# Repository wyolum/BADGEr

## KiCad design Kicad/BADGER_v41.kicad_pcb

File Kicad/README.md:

BADGEr
======

EReader badge and shield
new version (v4.1) with minor mods to the front silk legend. No hardware changes from v4

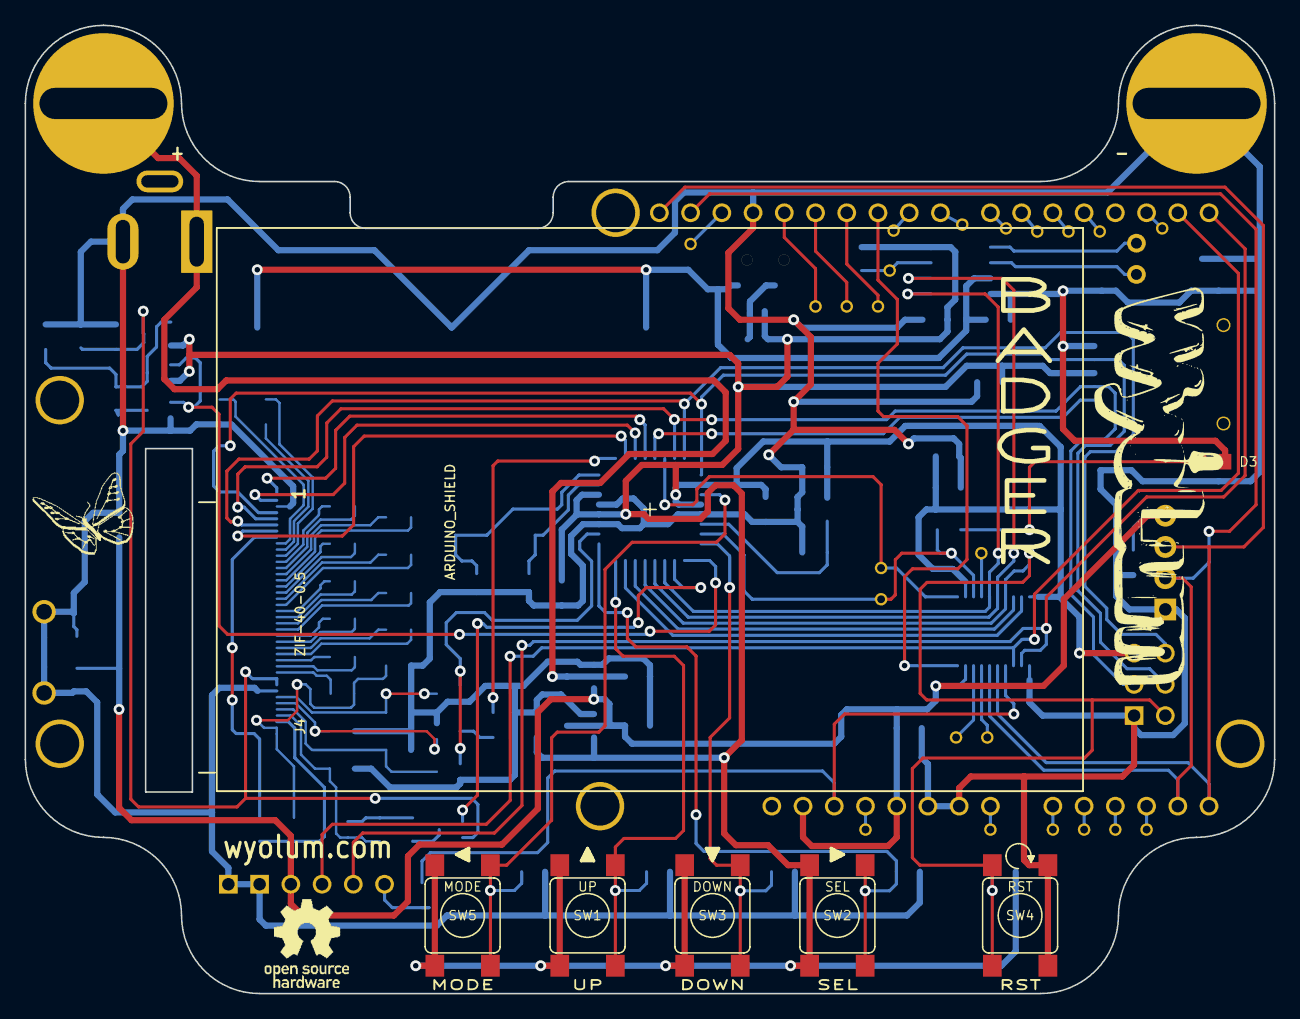
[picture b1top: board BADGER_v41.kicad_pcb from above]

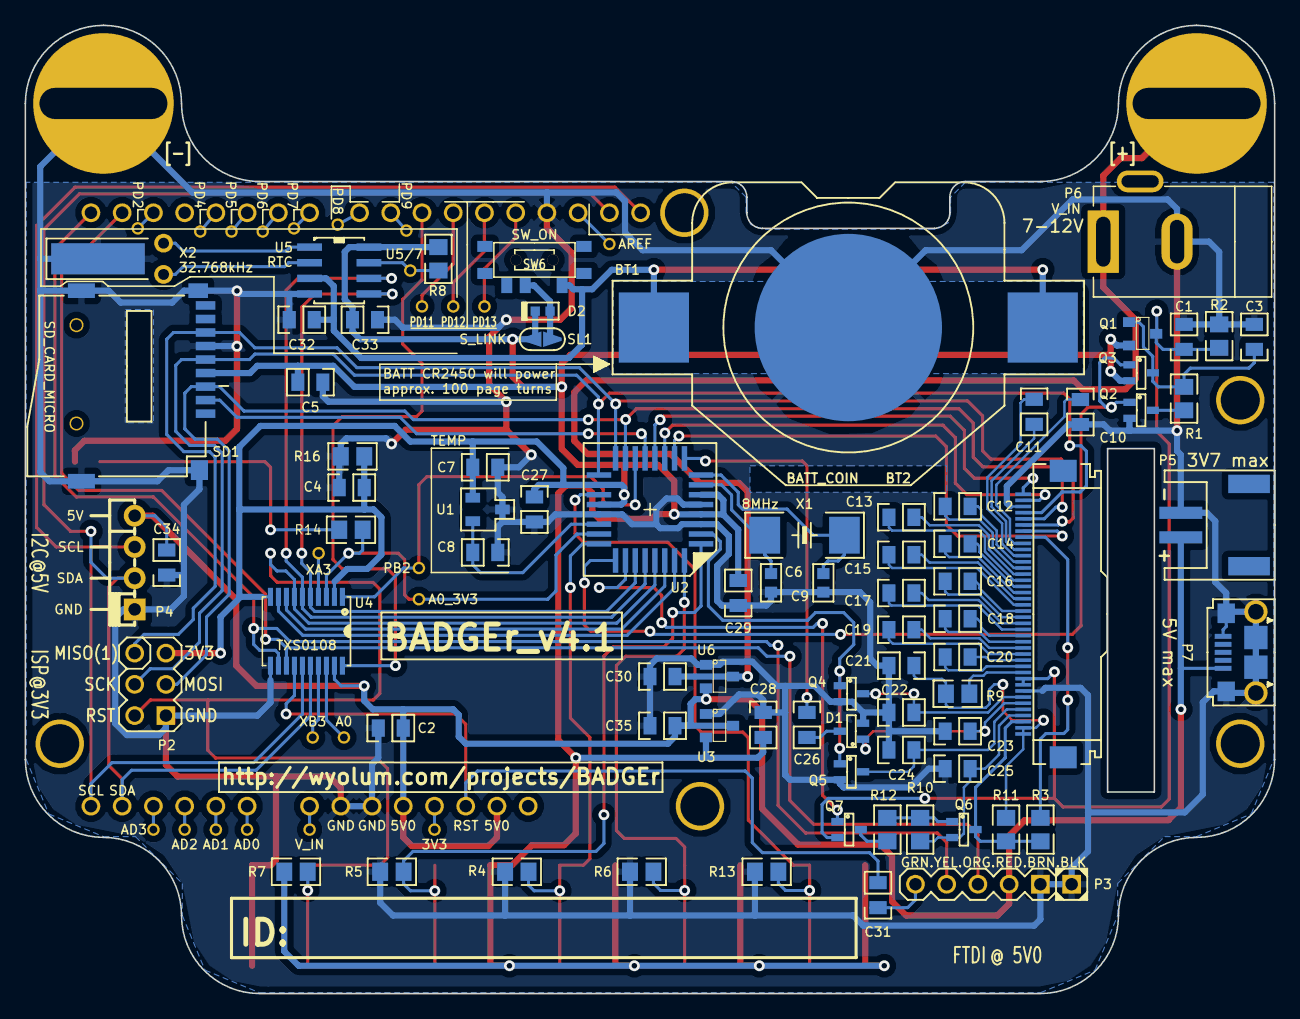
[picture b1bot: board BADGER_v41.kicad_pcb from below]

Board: 2 copper layers, 101.6 x 78.7 mm, 116 parts (101 on the bottom side), 97 nets.

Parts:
A0, A0_3V3: IO
AD0, AD1, AD2, AD3: IO; Breakout
AREF1: IO; Breakout
BT1: Batt_Clip; CR2450_SMD
BT2: BATT_COIN; CR2032
C1, C11, C12, C14, C17, C18, C19, C20, C24, C25, C28, C30, C35: 2.2u,16V; c_0805
C2, C3, C4, C5, C8, C26, C27, C29, C31, C32, C33, C34: 0.1u,16V; c_0805
C6, C9: 22pF; c_0603
C7: 1u,16V; c_0805
C10: 2.2u,10V; c_0805
C13, C15, C16, C22, C23: 2.2u,25V; c_0805
C21: 1u,10V; c_0805
D1: BAT54SW; SOT323
D2: DB2S20500L; d_VMD2
D3: DEBUG; led_0805
G1: WYO; wyo_logo
G4: OSHW; OSHW_logo
H1, H2, H5, H6: IO; vite_3mm
J4: ZIF-40-0.5; ZIF-40-0.5-M_seeed
P1: PCB
P2: ISP; Header_ISP
P3: FTDI; Header_FTDI
P4: C3SB; pin_strip_4-90
P5: JST_3V7; CONN_JST-2_SMD
P6: V_IN; JACK_ALIM
P7: UUSB_B; USB_B_Micro
PB2: IO
PD2, PD4, PD5, PD6, PD7, PD8, PD9, PD11, PD12, PD13: IO; Breakout
Q1: DMG2301U-7; SOT23
Q2, Q4, Q5, Q6: 2N7002KW; SOT323
Q3, Q7: BSS84W; SOT323
R1, R2: 33k; r_0805
R3: 0R(NC); r_0805
R4, R5, R6, R7, R8, R13, R16: 10k; r_0805
R9: 2k; r_0805
R10, R11, R12: 100k; r_0805
R14: 1k5; r_0805
SD1: SD_CARD_MICRO; SD_Micro_seeed
SHIELD1: ARDUINO_SHIELD; ARDUINO_SHIELD_040pins
SL1: S_LINK; ShortLink
SW1: UP; SW_SMD
SW2: SEL; SW_SMD
SW3: DOWN; SW_SMD
SW4: RST; SW_SMD
SW5: MODE; SW_SMD
SW6: SW_ON; SW_SLIDE_seeed
U1: MCP9700AT; SOT23-3-Temp
U2: ATMEGA328-AU-ND; TQFP32
U3: MCP1700T-33; SOT23
U4: TXS0108; TXS0108EPWR
U5: BQ32000; SO8E
U5/7: IO
U6: MCP1702T-50; SOT23
V1, V2: IO; Breakout
X1: 8MHz; Xtal_SMD
X2: 32.768kHz; XTAL_3
XA3: IO
XB3: IO

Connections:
/3V: SHIELD1.3V3, V2.1
/3V3: C4.1, C5.1, C7.2, C27.2, C28.1, C29.1, C33.1, D2.2, P2.2, Q1.2, Q3.2, R7.2, R8.2, R16.2, SD1.4, SL1.2, SW1.2, SW2.2, SW3.2, SW5.2, U1.1, U2.4, U2.6, U2.18, U2.20, U3.2, U4.2, U4.10, U5.8
//EPD_CS_3V3: J4.1, U2.12
//RESET_3V3: J4.7, U2.10
/A0: A0.1, U4.18
/A0_3V3: A0_3V3.1, R14.1, U2.23, U4.3
/AD0: AD0.1, SHIELD1.AD0
/AD1: AD1.1, SHIELD1.AD1
/AD2: AD2.1, SHIELD1.AD2
/AD3: AD3.1, SHIELD1.AD3
/BATT_3V: D2.1, SL1.1, SW6.2
/BATT_RTC: BT1.+, C32.1, SW6.1, U5.3
/BORDER: J4.38, Q6.3, R3.2, R11.1
/BORDER_CONTROL: Q7.1, U2.26
/BUSY_3V3: J4.2, U2.11
/C11M: C20.1, J4.28
/C11P: C20.2, J4.29
/C12M: C19.1, J4.26
/C12P: C19.2, J4.27
/C13M: C18.1, J4.24
/C13P: C18.2, J4.25
/C14M: C17.1, J4.22
/C14P: C17.2, J4.23
/C15M: C16.1, J4.20
/C15P: C16.2, J4.21
/C16M: C15.1, J4.18
/C16P: C15.2, J4.19
/C21M: C14.1, J4.16
/C21P: C14.2, J4.17
/C31M: C13.1, J4.14
/C31P: C13.2, J4.15
/C41M: C12.2, J4.13
/C41P: C12.1, J4.12
/C42M: C11.2, J4.11
/C42P: C11.1, J4.10
/DISCHARGE: Q4.1, Q5.1, U2.2
/DOWN: R4.2, SW3.1, U2.24
/DTR: C31.2, P3.6
/MODE: R13.2, SW5.1, U2.19
/PANEL_ON: Q2.1, Q3.1, U2.25
/PD2: PD2.1, SHIELD1.2
/PD4: PD4.1, SHIELD1.4
/PD5: PD5.1, SHIELD1.5
/PD6: PD6.1, SHIELD1.6
/PD7: PD7.1, SHIELD1.7
/PD8: PD8.1, SHIELD1.8
/PD9: PD9.1, SHIELD1.9
/PD11: PD11.1, SHIELD1.11
/PD12: PD12.1, SHIELD1.12
/PD13: PD13.1, SHIELD1.13
/PWM: C26.2, U2.9
/RST: C31.1, SHIELD1.RST, U4.14
/RST_3V3: P2.5, R7.1, SW4.2, U2.29, U4.7
/RXD: P3.4, SHIELD1.1, U4.13
/RXD_3V3: U2.30, U4.8
/SCL: P4.2, SHIELD1.AD5, SHIELD1.AD52, U4.15
/SCL_3V3: U2.28, U4.6, U5.6
/SDA: P4.3, SHIELD1.AD4, SHIELD1.AD42, U4.16
/SDA_3V3: U2.27, U4.5, U5.5
/SD_CS_3V3: SD1.2, U2.13
/SEL: R5.2, SW2.1, U2.1
/SPI_CLK_3V3: J4.4, P2.3, SD1.5, U2.17
/SPI_MISO_3V3: J4.6, P2.1, SD1.7, U2.16
/SPI_MOSI_3V3: J4.5, P2.4, SD1.3, U2.15
/SPI_SS: SHIELD1.10, U4.20
/SPI_SS_3V3: PB2.1, U2.14, U4.1
/SQW: R8.1, U5.7, U5/7.1
/TEMPERATURE: C8.1, U1.2, U2.22
/TXD: P3.5, SHIELD1.0, U4.12
/TXD_3V3: U2.31, U4.9
/UP: R6.2, SW1.1, U2.32
/VCC5V: C2.1, C34.1, C35.1, P3.3, P4.1, P5.1, P7.1, SHIELD1.5V_1, SHIELD1.5V_2, U3.3, U4.19, U6.2
/VCC_T: C1.2, J4.31, J4.32, Q1.3, Q7.2, R2.1
/VCL: C10.2, J4.9
/VCOM: C21.2, J4.39, J4.40, R9.2, R11.2
/VCOM_DRIVER: J4.30, R9.1
/VDH: C24.1, J4.36, Q5.3
/VDL: C25.1, J4.37, Q6.2, R10.2
/VGH: C22.1, J4.34, Q4.3
/VGL: C23.1, D1.1, J4.35
/VIN: SHIELD1.V_IN, V1.1
/V_IN: C30.1, H1.1, P6.1, U6.3
GND: BT1.-, C1.1, C2.2, C3.1, C4.2, C5.2, C6.1, C7.1, C8.2, C9.1, C10.1, C21.1, C22.2, C23.2, C24.2, C25.2, C27.1, C28.2, C29.2, C30.2, C32.2, C33.2, C34.2, C35.2, D1.2, D3.2, H2.1, J4.3, J4.33, P2.6, P3.1, P3.2, P4.4, P5.2, P6.2, P7.5, P7.T1, P7.T2, P7.T3, P7.T4, P7.T5, P7.T6, Q2.2, Q4.2, Q5.2, R2.2, R4.1, R5.1, R6.1, R13.1, R16.1, SD1.6, SD1.G1, SD1.G2, SD1.G3, SD1.G4, SHIELD1.GND1, SHIELD1.GND2, SHIELD1.GND3, SW4.1, U1.3, U2.3, U2.5, U2.21, U3.1, U4.11, U5.4, U6.1, X2.3
unnamed: C9.2, U2.8, X1.1
unnamed: C6.2, U2.7, X1.2
unnamed: Q2.3, R1.1
unnamed: U4.17, XB3.1
unnamed: C3.2, Q1.1, Q3.3, R1.2
unnamed: U4.4, XA3.1
unnamed: AREF1.1, SHIELD1.AREF
unnamed: D3.1, R14.2
unnamed: U5.2, X2.2
unnamed: U5.1, X2.1
unnamed: C26.1, D1.3
unnamed: J4.8, R3.1
unnamed: Q7.3, R12.2
unnamed: Q6.1, R10.1, R12.1

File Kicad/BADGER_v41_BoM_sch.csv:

Reference, Value, Footprint, Datasheet, Field4, Field5, Field6, Field7, Field8, Field9, Field10, Field11, Field12
Q5,2N7002KW,SOT323,
C20,2.2u,16V,c_0805,,0805/2.2u/16V/Y5V,,,,,,,,
R3,0R(NC),r_0805,,0402/0R/5%/(NC),DNP,,,,,,,
R11,100k,r_0805,,0402/100k/5%,,,,,,,,
C19,2.2u,16V,c_0805,,0805/2.2u/16V/Y5V,,,,,,,,
D1,BAT54SW,SOT323,
R2,33k,r_0805,,0402/33k/5%/(NC),DNP,,,,,,,
C25,2.2u,16V,c_0805,,0805/2.2u/16V/Y5V,,,,,,,,
C22,2.2u,25V,c_0805,,0805/2.2u/25V/Y5V,,,,,,,,
Q3,BSS84W,SOT323,
C14,2.2u,16V,c_0805,,0805/2.2u/16V/Y5V,,,,,,,,
C26,0.1u,16V,c_0805,,0603/100n/16V/X7R,,,,,,,,
Q7,BSS84W,SOT323,
C8,0.1u,16V,c_0805,,0603/0.1uF/16V,DNP,,,,,,,
C7,1u,16V,c_0805,,1u/10V/X7R,,,,,,,,
C21,1u,10V,c_0805,,1u/10V/X7R,,,,,,,,
C23,2.2u,25V,c_0805,,0805/2.2u/25V/Y5V,,,,,,,,
C12,2.2u,16V,c_0805,,0805/2.2u/16V/Y5V,,,,,,,,
C28,2.2u,16V,c_0805,,0805/2.2uF/16V/Y5V,,,,,,,,
C16,2.2u,25V,c_0805,,0805/2.2u/25V/Y5V,,,,,,,,
C24,2.2u,16V,c_0805,,0805/2.2u/16V/Y5V,,,,,,,,
J4,ZIF-40-0.5,ZIF-40-0.5-M_seeed,
C3,0.1u,16V,c_0805,,0402/0.1uF/16V/Y5V,,,,,,,,
R9,2k,r_0805,,0603/2k/5%,,,,,,,,
Q6,2N7002KW,SOT323,
C11,2.2u,16V,c_0805,,0805/2.2u/16V/Y5V,,,,,,,,
R1,33k,r_0805,,0402/33K/5%,,,,,,,,
C30,2.2u,16V,c_0805,,0805/2.2uF/16V/Y5V,,,,,,,,
C13,2.2u,25V,c_0805,,0805/2.2u/25V/Y5V,,,,,,,,
R12,100k,r_0805,,0402/100k/5%,,,,,,,,
Q4,2N7002KW,SOT323,
C10,2.2u,10V,c_0805,,0805/2.2u/10V/Y5V,,,,,,,,
Q1,DMG2301U-7,SOT23,
C17,2.2u,16V,c_0805,,0805/2.2u/16V/Y5V,,,,,,,,
Q2,2N7002KW,SOT323,
C18,2.2u,16V,c_0805,,0805/2.2u/16V/Y5V,,,,,,,,
C15,2.2u,25V,c_0805,,0805/2.2u/25V/Y5V,,,,,,,,
C1,2.2u,16V,c_0805,,0805/2.2u/10V/Y5V,,,,,,,,
U4,TXS0108,TXS0108EPWR,
R16,10k,r_0805,,0402/0R/5%,,,,,,,,
SD1,SD_CARD_Micro,SD_Micro_seeed,
R10,100k,r_0805,,0402/100k/5%,,,,,,,,
C2,0.1u,16V,c_0805,,0603/0.1uF/16V,,,,,,,,
C4,0.1u,16V,c_0805,,0603/0.1uF/16V,,,,,,,,
U1,MCP9700AT,SOT23-3-Temp,
C5,0.1u,16V,c_0805,,0603/0.1uF/16V,,,,,,,,
SW1,UP,SW_SMD,
SW2,SEL,SW_SMD,
SW3,DOWN,SW_SMD,
R4,10k,r_0805,,0402/0R/5%,,,,,,,,
R5,10k,r_0805,,0402/0R/5%,,,,,,,,
R6,10k,r_0805,,0402/0R/5%,,,,,,,,
P1,PCB,PCB,
U2,ATMEGA328-AU-ND,TQFP32,
X1,8MHz,Xtal_SMD,
C6,22pF,c_0603,,0603/0.1uF/16V,,,,,,,,
C9,22pF,c_0603,,0603/0.1uF/16V,,,,,,,,
SW4,RST,SW_SMD,
R7,10k,r_0805,,0402/0R/5%,,,,,,,,
A0_3V3,IO,IO,
P2,ISP,Header_ISP,,DNP,,,,,,,,
P3,FTDI,Header_FTDI,
C31,0.1u,16V,c_0805,,0603/0.1uF/16V,,,,,,,,
P4,C3SB,pin_strip_4-90,,DNP,,,,,,,,
H1,I/O,vite_3mm,
H2,I/O,vite_3mm,
U3,MCP1700T-33,SOT23,,MCP1700T-3302E/TT,,,,,,,,
P5,JST_3V7,CONN_JST-2_SMD,,DNP,,,,,,,,
C29,0.1u,16V,c_0805,,0603/0.1uF/16V,,,,,,,,
C27,0.1u,16V,c_0805,,0603/0.1uF/16V,,,,,,,,
PB2,IO,IO,
BT1,Batt_Clip,CR2450_SMD,,HOLDER BATTERY COIN 20MM DIA THM,Coin Cell, Retainer,Coin, 20.0mm,Keystone Electronics,3003,Digikey,3003K-ND,http://www.digikey.com/scripts/DkSearch/dksus.dll?x=0&y=0&la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,
BT2,Batt_Coin,CR2032,,BATTERY LITHIUM COIN 3V 20MM,Lithium, 3V, 225mAh,CR2032,Panasonic - BSG,CR2032,Digikey,P189-ND,http://www.digikey.com/product-detail/en/CR2032/P189-ND/3193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,
A0,IO,IO,
XB3,IO,IO,
X2,32.768kHz,XTAL_3,,,DNP,,,,,,,
R8,10k,r_0805,,0402/0R/5%,,,,,,,,
C32,0.1u,16V,c_0805,,0603/0.1uF/16V,,,,,,,,
SW5,MODE,SW_SMD,
R13,10k,r_0805,,0402/0R/5%,,,,,,,,
XA3,IO,IO,
C33,0.1u,16V,c_0805,,0603/0.1uF/16V,,,,,,,,
C34,0.1u,16V,c_0805,,0603/0.1uF/16V,,,,,,,,
U6,MCP1702T-50,SOT23,,MCP1700T-3302E/TT,,,,,,,,
C35,2.2u,16V,c_0805,,0805/2.2uF/16V/Y5V,,,,,,,,
P7,UUSB_B,USB_B_Micro,,DNP,,,,,,,,
D2,DB2S20500L,d_VMD2,
P6,V_IN,Connect:JACK_ALIM,,CONN POWER JACK MALE 2.5MM CLSD,Jack, Male,2.5mm ID, 5.5mm OD,CUI Inc,PJ-002B,Digikey,CP-002B-ND,http://www.digikey.com/product-detail/en/PJ-002B/CP-002B-ND/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,DNP
G1,WYO,wyo_logo,
U5/7,IO,IO,
H5,I/O,vite_3mm,
H6,I/O,vite_3mm,
SL1,S_LINK,ShortLink,
D3,DEBUG,led_0805,
R14,1k5,r_0805,,0402/100k/5%,,,,,,,,
SW6,SW_ON,SW_SLIDE_seeed,
AREF1,IO,Breakout,
PD13,IO,Breakout,
PD12,IO,Breakout,
PD11,IO,Breakout,
PD9,IO,Breakout,
PD8,IO,Breakout,
PD7,IO,Breakout,
PD6,IO,Breakout,
PD5,IO,Breakout,
PD4,IO,Breakout,
PD2,IO,Breakout,
AD3,IO,Breakout,
AD2,IO,Breakout,
AD1,IO,Breakout,
AD0,IO,Breakout,
SHIELD1,ARDUINO_SHIELD,ARDUINO_SHIELD_040pins,
V1,IO,Breakout,
V2,IO,Breakout,
U5,BQ32000,SO8E,,DNP,,,,,,,,
G4,OSHW,OSHW_logo,

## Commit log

2013-10-17 Initial commit for v5 of BADGEr
2013-10-18 changed to v4.1 and added Logo
2013-10-19 modified WyoLum logo on front legend
2013-10-20 changed ver no. from v5 to v4.1
2013-10-21 created Gerber and PDF files for production of ver 4.1
2014-04-12 moved Kicad files to folder. Added 3D case files
2014-06-20 BADGEr added Silk legend and Dimensions PDF Files
2015-06-11 minor mods, no need to regenerate gerbers
2015-08-28 checkin updated Arduino library and examples
2015-11-06 added laser cut enclosure files and photos
2015-11-11 try to clean up empty EPD directory
2015-11-11 Add in EPDV2 (G2 COG driver) files
2017-06-01 fix fading by sending 0 on spi bus, capitalization error on include
2018-07-30 upgraded wifit.py from py2 to py3
